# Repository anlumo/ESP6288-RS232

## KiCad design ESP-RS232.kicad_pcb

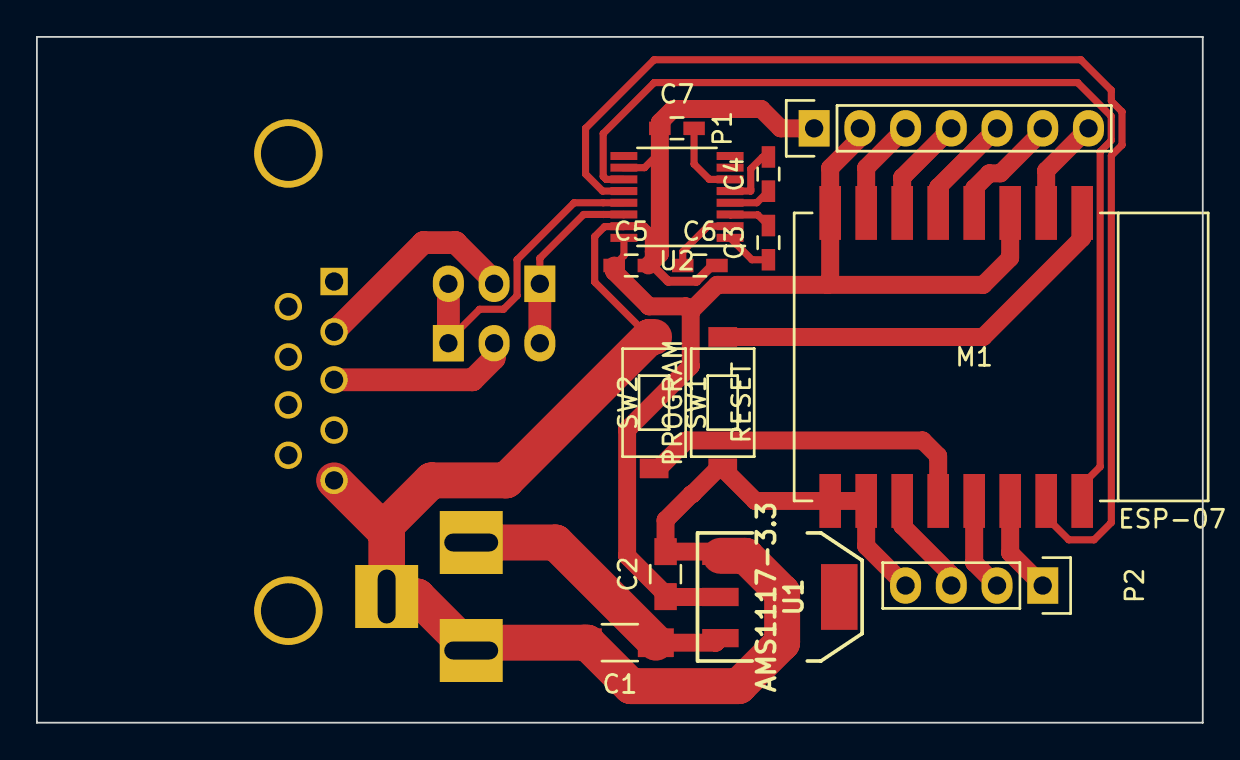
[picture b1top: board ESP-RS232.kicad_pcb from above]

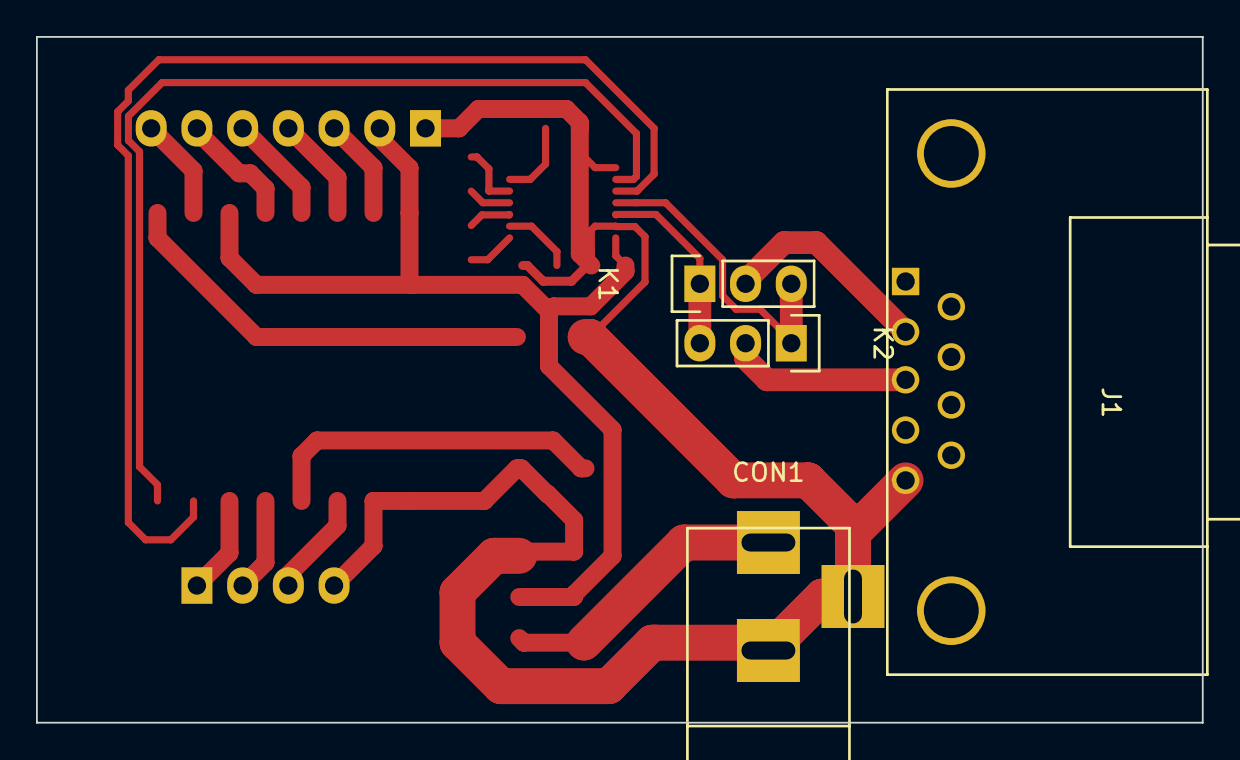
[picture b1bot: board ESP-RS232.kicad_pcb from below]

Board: 2 copper layers, 64.8 x 38.1 mm, 18 parts (4 on the bottom side), 25 nets.

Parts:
C1: 10µF; C_1206_HandSoldering
C2: 22µF; C_0805_HandSoldering
C3, C4, C5, C6, C7: 100nF; C_0603_HandSoldering
CON1: BARREL_JACK
J1: DB9; DB9FC
K1: PIN2; Pin_Header_Straight_1x03
K2: PIN3; Pin_Header_Straight_1x03
M1: ESP-07
P1: GPIO1; Pin_Header_Straight_1x07
P2: GPIO2; Pin_Header_Straight_1x04
SW1: RESET; Push Button Switch 3.5X6
SW2: PROGRAM; Push Button Switch 3.5X6
U1: AMS1117-3.3; SOT223
U2: MAX232; TSSOP-16_4.4x5mm_Pitch0.65mm

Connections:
+3.3V: C2.1, C5.1, M1.3, M1.8, P1.2, U1.2, U2.16
GND: C1.2, C2.2, C5.2, C6.2, C7.1, CON1.2, CON1.3, J1.5, M1.9, M1.10, P1.1, P2.4, SW1.1, SW2.2, U1.1, U2.10, U2.15
unnamed: C1.1, CON1.1, U1.3
unnamed: C3.1, U2.1
unnamed: C3.2, U2.3
unnamed: C4.1, U2.4
unnamed: C4.2, U2.5
unnamed: C6.1, U2.2
unnamed: C7.2, U2.6
unnamed: J1.2, K1.2
unnamed: J1.3, K2.2
unnamed: K1.1, K2.3, U2.14
unnamed: K1.3, K2.1, U2.13
unnamed: M1.1, SW1.2
unnamed: M1.2, P1.7
unnamed: M1.4, P1.6
unnamed: M1.5, P1.5
unnamed: M1.6, P1.4
unnamed: M1.7, P1.3
unnamed: M1.11, P2.3
unnamed: M1.12, SW2.1
unnamed: M1.13, P2.2
unnamed: M1.14, P2.1
unnamed: M1.15, U2.12
unnamed: M1.16, U2.11

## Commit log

2015-03-27 Initial commit (should work already).
